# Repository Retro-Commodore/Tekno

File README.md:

# Tekno
Tekno kit from Catus - Electronics controller using your Amiga

Yet another reverse product from e5frog.

https://bigbookofamigahardware.com/bboah/product.aspx?id=722

#

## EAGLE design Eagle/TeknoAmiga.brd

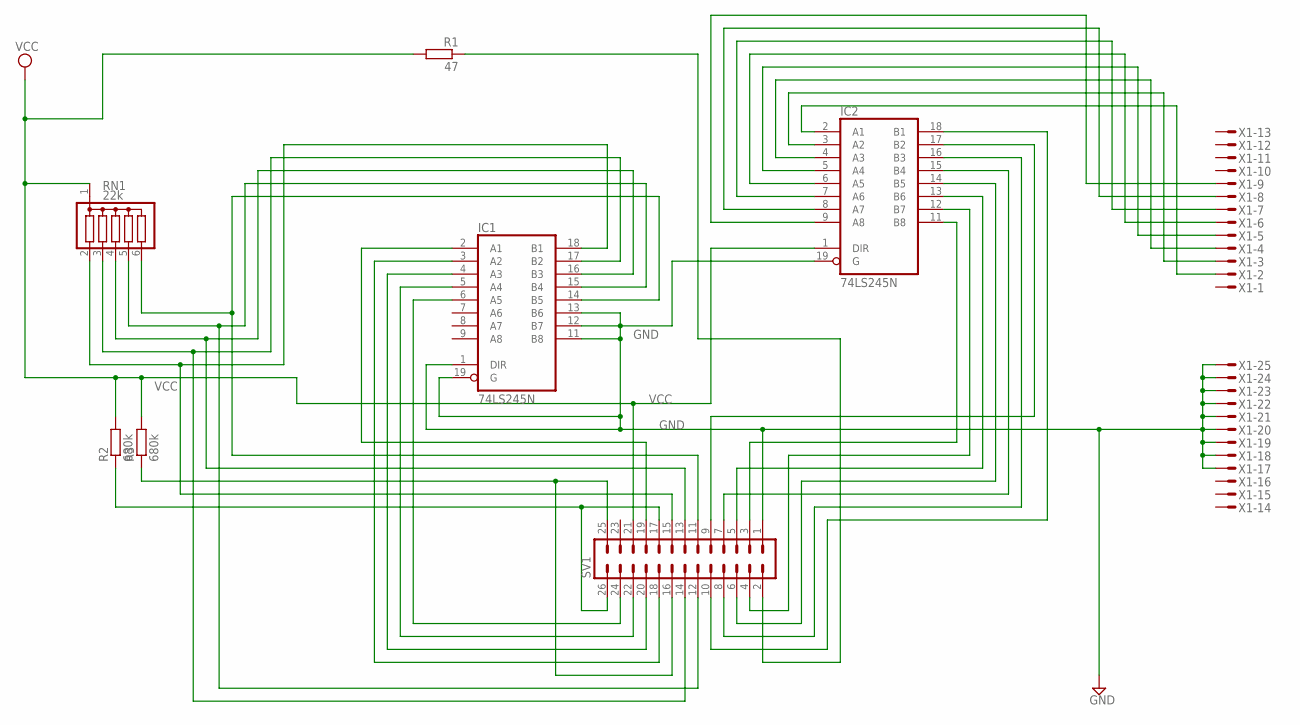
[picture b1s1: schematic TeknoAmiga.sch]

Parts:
IC1, IC2: 74LS245N; DIL20
R1: 47; 0207/12
R2, R3: 680k; 0207/12
RN1: 22k; SIL6
SV1: MA13-2
X1: M25HPS; M25HP

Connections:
GND: IC1.1 (DIR), IC1.10 (GND), IC1.11 (B8), IC1.12 (B7), IC1.13 (B6), IC1.19 (G), IC2.10 (GND), IC2.19 (G), SV1.1, X1.17, X1.18, X1.19, X1.20, X1.21, X1.22, X1.23, X1.24, X1.25
unnamed: IC2.2 (A1), X1.2
unnamed: IC2.3 (A2), X1.3
unnamed: IC2.4 (A3), X1.4
unnamed: IC2.5 (A4), X1.5
unnamed: IC2.6 (A5), X1.6
unnamed: IC2.7 (A6), X1.7
unnamed: IC2.8 (A7), X1.8
unnamed: IC2.9 (A8), X1.9
unnamed: IC1.14 (B5), RN1.6, SV1.11
unnamed: IC1.15 (B4), RN1.5, SV1.12
unnamed: IC1.16 (B3), RN1.4, SV1.13
unnamed: IC1.17 (B2), RN1.3, SV1.14
unnamed: IC1.18 (B1), RN1.2, SV1.15
unnamed: R2.1, SV1.17, SV1.26
unnamed: R3.1, SV1.16, SV1.25
unnamed: IC1.6 (A5), SV1.24
unnamed: IC1.5 (A4), SV1.22
unnamed: IC1.4 (A3), SV1.20
unnamed: IC1.3 (A2), SV1.18
unnamed: IC1.2 (A1), SV1.19
unnamed: R1.1, SV1.2
unnamed: IC2.11 (B8), SV1.3
unnamed: IC2.12 (B7), SV1.4
unnamed: IC2.13 (B6), SV1.5
unnamed: IC2.14 (B5), SV1.6
unnamed: IC2.15 (B4), SV1.7
unnamed: IC2.16 (B3), SV1.8
unnamed: IC2.17 (B2), SV1.9
unnamed: IC2.18 (B1), SV1.10
VCC: IC1.20 (VCC), IC2.1 (DIR), IC2.20 (VCC), R1.2, R2.2, R3.2, RN1.1, SV1.21

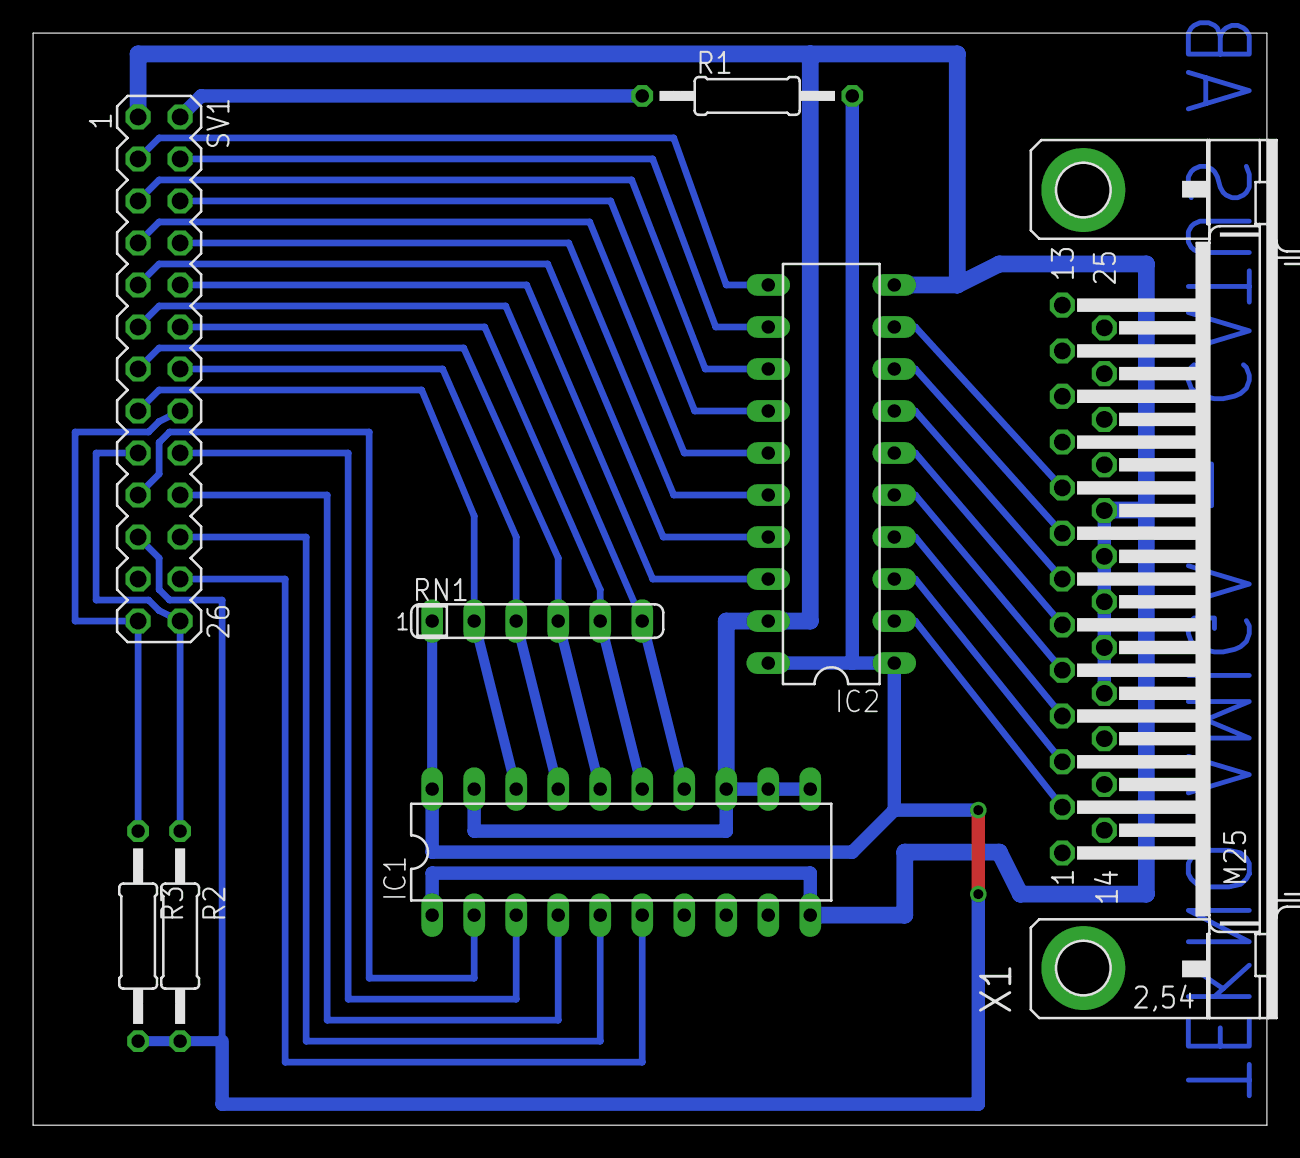
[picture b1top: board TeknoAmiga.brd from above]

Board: 2 copper layers, 74.6 x 66.0 mm, 8 parts (0 on the bottom side), 31 nets.

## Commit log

2023-05-29 added kicad version + 3d image
2023-05-29 remove backups
